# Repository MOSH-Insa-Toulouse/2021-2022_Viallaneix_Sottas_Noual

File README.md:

# 2021-2022_Viallaneix_Sottas_Noual MOSH Project 2022
Granulometric sensor

# Informations générales
> Ce projet s'inscrit dans le cadre de l'UF _"Du capteur au banc de test en open source hardware"_.
> Le cœur du projet bat sur la fréquence de la **LOW TECH**. Nous partirons de la fabrication d'un capteur granulométrique élaboré à partir d'une feuille de papier sur laquelle une couche de carbone sera déposée à l'aide d'un crayon à papier (panel de dureté entre HB et 9B) selon un motif prédeterminé. À ce corps d'épreuve, deux électrodes insérées aux extrémités du motif permettront la circulation d'un courant. Une déformation du capteur entraînera une variation du courant mesurable par un système d'acquisition de données. Les enjeux du projet sont donc multiples!
* **Physique** : sur les propriétés d'un capteur granulométrique
* **Technique** : sur la conception et le développement d'un système d'acquisition
* **Exploratoire** : par l'utilisation des outils et concepts de l'Open Source Hardware.
* **Se construire une composante _low-tech_  de l'ingénieur que nous serons** : en s'interrogeant sur les attentes d'une société en mutation, en posant un regard critique sur la notion de progrès technique et sa finalité.

# Ce que fait ce projet 

> La finalité du projet est de pouvoir estimer les forces et faiblesses de ces capteurs low-tech. Pour cela nous allons devoir les tester, déterminer leurs caractéristiques et leur limites d'utilisations.
> Pour y parvenir, nous allons concevoir un banc de mesures qui nous permettra, dans un premier temps, d'étalonner les capteurs (leurs sensibilités varient en fonction de la dureté) puis, dans un deuxième temps, de les éprouver dans des conditions et durées d'utilisation controlées.
> Les jeux de données issues de ces tests vont devenir rapidement conséquents et il sera utile de prévoir les scripts et la visualisation en sortie du banc de test et étalonnage. 
> La composante **étalonnage** du banc permet de détérminer la sensibilité un capteur de sensibilité inconnue. La composante **test** permet de soumettre le capteur à des séries de flexion/déflexion fonction d'un angle compris entre -85 et +85 degrés par rapport à la position d'équilibre.
> Dans la suite du projet le capteur désignera le corps d'épreuve et le banc de test permettant l'acquisition des données.

***
## Les axes du projets
* [Présentation du capteur granulométrique](#présentation-du-capteur-granulométrique)
* [Acquisition des données](#acquisition-des-données)
  * [Carte Arduino](#la-carte-arduino)
  * [Étude du circuit électrique](#le-conditionneur)
    * [Partie 1: Mesure d'un très faible courant avec l'aide d'un micro-contrôleur](#partie-1-mesure-dun-très-faible-courant-avec-laide-dun-micro-contrôleur)
       * [Vérification avec la Datasheet de l'AOP](#vérification-avec-la-datasheet-de-laop)
    * [Partie 2: Mise en oeuvre du filtrage du signal](#partie-2-mise-en-oeuvre-du-filtrage-du-signal)
    * [Schéma du circuit électronique final](#schéma-du-circuit-électronique-final)
    * [Partie 3: Simulations sous *LTSpice*](#partie-3-simulations-sous-ltspice)
  * [Code Arduino du système](#code-arduino-du-système)
  * [Application sur Android](#application-sur-android)
* [Réalisation du PCB](#réalisation-du-pcb)
   * [Partie 1: Conception de la schématique et des connexions entre les composants électroniques](#partie-1-conception-de-la-schématique-et-des-connexions-entre-les-composants-électroniques)
   * [Partie 2: Conception du PCB](#partie-2-conception-du-pcb)
   * [Partie 3: Soudure des composants sur le PCB et premiers tests](#partie-3-soudure-des-composants-sur-le-pcb-et-premiers-tests)
* [Banc de tests](#banc-de-tests)
* [Measurement System Analysis](#measurement-system-analysis)
* [Crédits](#auteurs)

***

### Présentation du capteur granulométrique
> Le capteur sélectionné dans le cadre de ce projet est un dépôt de graphite sur un papier, effectué à l’aide d’un crayon plus ou moins gras. 
Nous utiliserons pour cela la résistivité du graphite, qui est suffisamment faible pour laisser circuler un courant mesurable. Néanmoins, avec cette résistivité de 8 µΩ.m (contre 0,017 µΩ.m pour le cuivre), il faudra utiliser un montage amplificateur dans notre banc de test.

> Le dépôt de graphite effectué sur le papier sera alors représentatif de la flexion que ce dernier subit : les grains de graphite jouent le rôle de conducteur mais leur éloignement variera selon la flexion, et va donc influencer la résistance mesurée.

<div align="center">
</p>

**Figure 1: Première description schématique d'une mesure sur le capteur de graphite**

<div align="left"></p>

> Dans l’exemple ci dessus, on mesurera pour une même tension appliquée que:

<div align="center">
</p>

<div align="left"></p>

> L’intérêt de ce capteur se situe dans son aspect low-tech qui lui permet d’être facilement produit, mais pas uniquement :  la vaste gamme de dureté des mines de crayon (H, F, HB, B) offre un large choix pour la résistivité du dépôt.
En effet, la dureté d’une mine correspond à ses proportions de graphite et d’argile. Le graphite est, par exemple, plus présent dans un crayon dit « gras » de type B que dans un crayon de type H. Ainsi, nous disposons assez simplement d’un large panel de capteurs pour éventuellement les comparer à l’aide du banc de tests.

(#### Propriété d'un système granulaire)
### Acquisition des données
#### La carte Arduino

Dans notre projet, nous allons utiliser la carte Arduino UNO possédant le microcontrôleur ATMega328. 

<div align="center">
</p>

**Figure 2: Illustration de la carte Arduino UNO et Brochage de la carte Arduino**

<div align="left"></p>

Elle dispose de 6 entrées analogiques et de 14 broches numériques d'entrées/sorties. 
Pour pouvoir l'utiliser, on a juste à la connecter directement à l'ordinateur via le câble USB. 

La carte Arduino UNO possède les caractéristiques suivantes: 

* **Résolution**: 10 à 12 bits (1024 à 4096 points)
* **Pleine échelle (VRef)**: de 1.1 V à 5.0 V
* **Impédance de source max**: 1 kΩ à 10 kΩ
* **Fréquence d'échantillonnage**: 15 kHz maximale

#### Le conditionneur

#### Partie 1: Mesure d'un très faible courant avec l'aide d'un micro-contrôleur
L’objectif étant d’extraire l’information utile du capteur ayant un très faible courant (environ 100 nA), le montage électrique doit être adapté de manière à mesurer des courants faibles. Selon les caractéristiques techniques du microcontrôleur Arduino (cf Datasheet), on ne peut pas mesurer directement de très faibles courants en raison de l’impédance de source (environ égale à quelques kOhms). Il est donc nécessaire d’utiliser un circuit amplificateur transimpédance composé d’un amplificateur opérationnel AOP pour convertir un courant issu du capteur en une tension mesurable par le CAN (Convertisseur Analogique-Numérique) de l’Arduino UNO.

<div align="center"></p>
  
**Figure 3: Montage de transimpédance (ou convertisseur courant-tension)**
  
<div align="left"></p>

L’inconvénient d’un montage classique de transimpédance est qu’il nécessite une grande résistance pour amplifier le signal et que la tension d’alimentation du capteur doit être négative. On peut donc ajouter un autre étage inverseur à la suite du premier montage : 

<div align="center"></p>
  
**Figures 4 et 5: Ajout d'un étage inverseur sur le montage de transimpédance et Calcul du gain du second montage**

<div align="left"></p>

Dans le montage ci-dessus, le gain du second étage étant négatif compte-tenu de son caractère inverseur (`cf Figure 3`), la résistance R1 du premier étage n’a plus besoin d’avoir une grande valeur. De plus, l’alimentation du capteur est donc positive grâce au second montage inverseur du fait des produits des gains de deux étages. 

Pour plus de simplicité, on a choisi un montage en prenant un seul AOP dans le montage.

<div align="center"></p> 

**Figure 6: Solution simplifiée pour le montage transimpédance**

**Figure 7: Calcul de la tension aux bornes de R1**

<div align="left"></p>
  
En calculant la tension aux bornes de la résistance R1, on obtient une tension environ égale à 10 mV d'après la `Figure 4`.

Il s’agit d’une valeur importante pour le choix de l’AOP notamment pour l'effet de l’offset du signal d’entrée. 
Le Gain de ce montage et la Tension de sortie ADC sont décrits dans les calculs ci-dessous : 

<div align="center"> </p>
  
**Figure 8: Calculs du gain du montage et de la tension de sortie**

<div align="left"></p>
  
Si on a un courant nul en entrée, on veut alors obtenir une tension ADC nulle en sortie, cela implique qu’il n’y ait pas de dérives en tension de la part de l’AOP.
Les principales contraintes pour le choix de l’amplificateur opérationnel sont le faible courant d’entrée et un très faible offset de tension devant être négligeable devant 10mV (tension aux bornes de R1).

##### Vérification avec la Datasheet de l'AOP

Selon les données de la [Datasheet](LTC1050C.pdf) de l'AOP 1050C, on constate qu'il possède un faible offset de tension d'environ 5μV au maximum et un très faible drift pour l'offset de tension à environ 0.05μV/°C. Cela indique la bonne stabilité de l'amplificateur opérationnel. Par comparaison, les AOP utilisés traditionnellement en salle de TP possèdent un offset autour de 5mV, une valeur 1000 fois plus grande que celle du 1050C.
En comparant la tension d'entrée (autour de 10mV `cf Figure 5`), on constate que l'offset de 5μV est très faible.
De plus, on peut remarquer que cet AOP possède un mode commun incluant la masse ce qui correspond à notre montage électrique.
  
<div align="center"></p>

**Figure 9: Extrait de la datasheet dans la partie Electrical Characteristics**

<div align="left"></p>
  
Enfin, on constate que le courant de polarisation en entrée (Input Bias Current) est au maximum égale à 30pA, cela convient car nous effectuons des mesures de courant autour de 100nA. Il faut que le courant Isense `cf Figure 4` soit très faible devant 100nA et le reste du courant passe dans la résistance R1. 
En respectant les différentes conditions énoncées précédemment, l'AOP 1050C est adapté pour notre circuit électronique.

#### Partie 2: Mise en oeuvre du filtrage du signal

Étant donné que ce montage est très sensible aux signaux parasites (50Hz, horloge du microcontrôleur Arduino, Bluetooth entre autres), on doit mettre en œuvre un filtrage passe-bas pour limiter les perturbations du signal.
D’une part, il faut appliquer un filtre passif en entrée pour limiter les perturbations de type radiofréquences pouvant conduire à un excès de bruit dans l’ADC.
Ensuite, on applique un filtre actif au niveau de l’amplificateur opérationnel pour augmenter l’efficacité de l’échantillonnage du signal. 
À la sortie de l’AOP, on utilise un dernier filtre passif pour retirer le bruit sur le traitement du signal et les phénomènes de repliement de spectre (aliasing). 

En intégrant les différents filtres, le montage ressemble à ceci : 

<div align="center"></p>

**Figure 10: Schéma du montage électrique avec les différents filtres**

<div align="left"></p>

On distingue 3 différents filtres où nous avons cherché pour chacun la fréquence de coupure et son rôle principal pour le filtrage : 

<div align="center"></p>

**Figure 11: Identification des différents filtres dans le montage**

<div align="left"></p> 
 
Tout d'abord, le filtre passe-bas passif, placé à l'entrée de l'AOP, est constitué de R1(100kΩ) et C1(100nF). Il possède une fréquence de coupure théorique environ égale à 16Hz `cf Figure 7` . Il permet donc de filtrer les perturbations et les excès de bruit en courant sur la forme du signal d'entrée. 

<div align="center"></p> 

**Figure 12: Calcul de la fréquence de coupure du filtre passif (R1 et C1)**

<div align="left"></p>

Ensuite, le filtre passe-bas actif, placé entre l'entrée et la sortie de l'AOP, est constitué de R3(100kΩ) et C4(1μF) en parallèle. Ce dernier possède une fréquence de coupure théorique environ égale à 1.6Hz `cf Figure 8`. Son rôle principal est de supprimer la composante parasite de 50Hz (du fait du couplage capacitif avec la tension 230V) qui perturbe significativement le signal `cf Figure XX`.

<div align="center"></p>

**Figure 13: Calcul de la fréquence de coupure du filtre actif (R3 et C4)**

<div align="left"></p>

Enfin, le filtre passe-bas passif, placé à la sortie de l'AOP, est constitué de R6(100kΩ) et C2(100nF). Il possède une fréquence de coupure théorique environ égale à 1.6kHz `cf Figure 9`. En sachant que la fréquence d'échantillonnage du micro-contrôleur est environ égale à 15,4kHz, il faut respecter la condition d'échantillonnage de Shannon à savoir:  

<div align="center"></p> 

</p>
</p>
</p>

**Figures 14: Calcul de la fréquence de coupure du filtre passif (R6 et C2) et Vérification de la condition d'échantillonnage de Shannon**

<div align="left"></p>

Selon les calculs, on respecte bien la condition d'échantillonnage de Shannon `cf Figure ci-dessus`, le filtre permet de limiter les effets de repliement de spectre (rôle d'anti-aliasing) et de manière générale, le bruit lors du traitement du signal. 

#### Schéma du circuit électronique final
> Voici un première proposition du schéma électrique
  
<div align="center"></p>

**Figure 15: Premier schéma du montage électronique**

<div align="left"></p>
  
Dans ce schéma, nous simulons le bruit en courant à l'entrée en mettant une capacité à côté du générateur de tension. On a ajouté une capacité C3 pour filtrer le bruit de la source d'alimentation.
  
> On propose une optimisation du montage électronique en simulant le capteur de graphite `cf Figure ci-dessous`
  
<div align="center"></p>

**Figure 16: Schéma électrique optimisé**

<div align="left"></p>
  
Nous avons simulé notre capteur de graphite (cf rectangle en haut à gauche de la `figure précédente`). 
> Commentaires à ajouter

#### Partie 3: Simulations sous *LTSpice*
  
On vérifie les conditions optimales de fonctionnement du montage électronique en effectuant différentes simulations sur le logiciel *LTSPice* `cf figures ci-dessous`.

<div align="center"></p>
</p>

**Figure 17: Vérification du gain d'amplification du signal environ égal 100**
  
</p>

**Figure 18: Vérification du la tension de sortie du montage avec un courant d'entrée égal à 100nA**

<div align="left"></p>
  
Pour l'illustration graphique du gain du montage général, on distingue qu'il y a bien 3 filtres dans le circuit électronique grâce aux différentes variations du terme de phase (courbe en traits en pointillés `cf Figure ci-dessous`).

<div align="center"></p>
</p>

**Figure 19: Identification graphique des 3 filtres**

<div align="left"></p>

> On vérifie graphiquement la fréquence de coupure de chaque filtre en effectuant une simulation fréquentielle (AC Sweep):

Pour le premier filtre à l'entrée de l'AOP (R1 et C1):
<div align="center">
</p>

**Figure 20: Illustration graphique de la fréquence de coupure du filtre (R1 et C1)**

<div align="left"></p>
  
Pour le second filtre entre l'entrée et la sortie de l'AOP (R3 et C4) et le dernier filtre à la sortie (R6 et C2):
  
<div align="center">
</p>

**Figure 21: Illustration graphique des fréquences de coupure des deux filtres passe-bas**

<div align="left"></p>

> On vérifie l'incidence du courant d'entrée de l'amplificateur sur la tension de sortie par une simulation temporelle:

<div align="center">
</p>

**Figure 22: Illustration graphique de l'incidence du courant d'entrée sur la tension de sortie**

<div align="left"></p>
  
On peut remarquer dans cette image qu'à partir d'une valeur de 500nA pour le courant d'entrée, on obtient une tension pouvant saturer le convertisseur analogique-numérique de l'Arduino. 

> On observe graphiquement l'atténuation globale du signal d'un bruit en courant de 50 Hz ainsi que celle associée à un bruit en courant à la fréquence de repliement de spectre autour de 7 kHz. 

<div align="center">
</p>

**Figures 23 et 24: Illustration graphique de l'atténuation du signal d'un bruit en courant pour deux fréquences spécifiques et calculs des atténuations**

<div align="left"></p>

Comme on peut le voir avec les calculs précédents, on constate qu'il y a une atténuation en bruit de courant environ égale à 40dB pour une fréquence autour de 50Hz et elle est environ égale à 100 dB pour un bruit en courant au voisinage de la fréquence de repliement de spectre. Cela montre bien que le signal peut être fortement perturbé et atténué si on laisse la composante fréquentielle à 50 Hz et si on ne respecte la condition d'échantillonnage.   

### Code Arduino du système
<div align="center">
</p>

**Figure 25: Logigramme de notre code Arduino**

<div align="left"></p>
  
Voici une présentation graphique de notre code Arduino.
  
### Application sur Android

L'application mobile associée au banc de test fonctionne avec un timer identique à celui du programme Arduino. L'utilisateur peut se connecter au module Bluetooth de son choix, puis vérifie que la connexion est bien établie avec un second bouton. Il peut ensuite lancer la mesure et afficher les résultats reçus sur un graphe en temps réel, afin de suivre l'évolution de la résistance du capteur. Le graphe reprend du début lorsque le balayage atteint le bout de l'écran, mais l'utilisateur peut le réinitialiser à sa guise avec un autre bouton. Enfin, la mesure peut être arrêtée en appuyant à nouveau sur le bouton qui l'a déclenché.

<div align="center"></p>
</p>

**Figure 26: Aperçu visuel de notre application**

<div align="left"></p>

<div align="center">
</p>
</p>

**Figures 27 et 28: Extraits des blocs pour la réalisation de l'application Android sur *MIT App Inventor***

<div align="left"></p>   

### Réalisation du PCB

Après avoir réalisé les simulations sur *LTSpice*, nous avons conçu un premier modèle de PCB avec l'aide du logiciel *KiCAD*. 

#### Partie 1: Conception de la schématique et des connexions entre les composants électroniques

> Lors de cette étape, nous avons choisi un modèle basé sur l'Arduino UNO pour avoir les bonnes dimensions de la carte et les pins de connexion adéquats. Afin de réaliser précisément le PCB, nous avons dû concevoir certains composants électroniques nous-mêmes dans la partie Schématique (écran OLED, module Bluetooth, l'amplificateur LTC1050C, l'encodeur rotatoire et le potentiomètre digital)  `cf Figures ci-dessous`

<div align="center">
</p>

**Figure 29: Schéma des pins de connexion de la carte Arduino UNO **

</p>
 
**Figure 30: Schéma du circuit électronique**
 
</p>
</p>
</p>
</p>

**Figures 31: Schémas et empreintes de chacun de nos composants électroniques (Écran OLED, BLuetooth, Encodeur rotatoire, Potentiomètre digital)**

<div align="left"></p>

#### Partie 2: Conception du PCB

> Dans cette partie, nous plaçons virtuellement les différents composants sur le PCB et nous effectuons toutes les connexions entre les pins de composants et ceux de la carte Arduino. Nos différents professeurs réferents (Mr Jérémie Grisolia et Mme Catherine Crouzet) nous ont indiqués les consignes à respecter pour la réalisation du PCB: 
  
* Largeur des pistes = 0.6 mm
* Largeur d'isolation des pistes = 0.9 mm
* Dimensions du trou pour l'écran OLED, le module Bluetooth et l'encodeur rotatoire = 2 mm * 2.5 mm
* Diamètre du via (trou entre la face avant et arrières du PCB) = 2 mm
* Taille du trou de perçage du via = 0.8 mm
* Taille du trou de perçage pour l'écran OLED, le module Bluetooth et l'encodeur rotatoire, l'AOP et le potentiomètre digital = 1 mm
* Dimensions du trou pour le support de l'AOP (pad n°1 rectangulaire et les autres pins sont ovales) = 2 mm * 2.5 mm
* Taille du trou de perçage pour les résistances et les capacités = 0.8 mm
  
<div align="center">
</p>

**Figure 32: Schémas des pistes sur le PCB**

<div align="left"></p>

<div align="center">
</p>

**Figure 33: Schéma 3D des pistes sur le PCB**

<div align="left"></p>
  
Avec l'aide de Mme Catherine Crouzet, nous avons réalisé le PCB selon le protocole suivant:

* Insolation de la plaque de résine positive par photo-lithographie UV par contact avec un masque `cf Figure ci-dessous` imprimé sur un film transparent, provenant du logiciel *KiCAD*. Cette résine est choisie de telle manière à être sensible aux rayons UV.
Une fois l'insolation réalisée, la partie de la résine insolée est dissoute dans une solution de développeur. Le reste de la résine, étant protégé par le masque, reste intact. On observe l'apparition des pistes du circuit sur le PCB.
  
* Passage dans un bain de péroxyde de fer pour enlever les résidus de la piste de cuivre sur le PCB
  
* Nettoyage et Séchage de la plaque à l'eau naturelle

<div align="center">
</p>

**Figure 34: Masque imprimé du PCB sur un film transparent**

<div align="left"></p>

#### Partie 3: Soudure des composants sur le PCB et premiers tests
 
Uns fois le PCB réalisé, nous avons percé tous les trous des pins associés à chaque composant électronique puis nous avons soudé les différents composants et les broches latérales entre le PCB et la carte Arduino.

### Banc de tests

> Le but de ce banc de test est de déterminer la sensibilité du capteur, de voir l’évolution de cette dernière selon la répétition des flexions et de comparer ces données avec un capteur commercialisé "Flex-Sensor".

> Ce banc de test est composé d’un servomoteur pour une bonne précision sur les angles, ainsi que d’un support où l’on vient encastrer le capteur. Une roue où l’on positionne le bout du capteur est alors entraînée par le servomoteur et génère la flexion. Il est fait de plaques de contreplaqué superposées, qui ont été découpées au FabLab et il permet de garder le capteur le plus intact possible, car celui-ci n’est maintenu qu’aux deux extrêmités et non pas sur le dépôt de graphite lui-même.
L’utilisateur détermine au préalable le nombre de répétitions souhaité à l’aide de l’encodeur rotatoire placé sur le PCB. Il peut ensuite récupérer les données (angle, itération de la mesure, résistance lue) sur le moniteur série et les traiter dans un logiciel comme Rmarkdown, Python via l'interpréteur Spyder IDE ou Qtiplot.
Le capteur qui servira de référence comparative sera le Flex Sensor fourni dans le kit Arduino, qui possède déjà une datasheet.

> Nous avons élaboré un premier modèle en 2D ainsi qu'un modèle 3D de notre banc de tests: 
<div align="center"></p>

**Figure 35: Dessin 2D du banc de test**

<div align="left"></p>
<div align="center"></p>

</p>

**Figure 36: Dessin 3D du banc de test sur *FreeCAD***

<div align="left"></p>

> Nous l'avons ensuite réalisé au FabLab avec l'aide d'une découpe laser: 

<div align="center">
</p>

**Figure 37: Réalisation du banc de test au FabLab**

<div align="left"></p>

Nous avons ensuite effectué les premiers tests sur notre banc de tests avec notre capteur: 

<div align="center">
</p>

**Figure 38: Premiers tests avec notre banc de tests**

<div align="left"></p>

### Measurement System Analysis

### Auteurs

Arona SOTTAS, Léo VIALLANEIX et Raphaël NOUAL

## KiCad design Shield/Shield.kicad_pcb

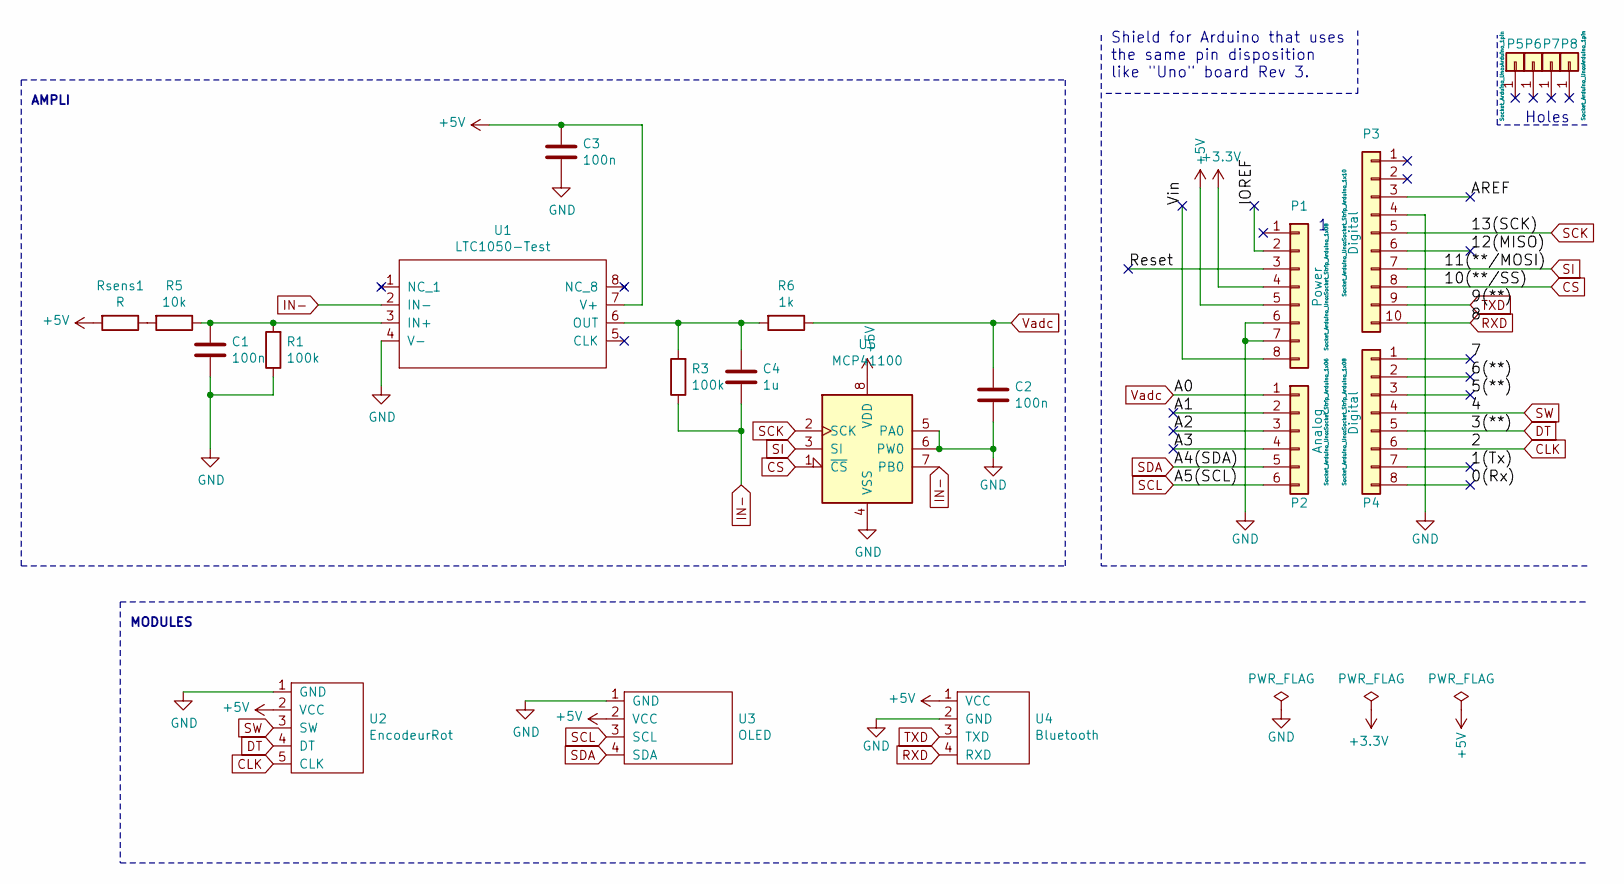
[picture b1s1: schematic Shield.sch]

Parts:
C1, C2, C3: 100n; C_Disc_D3.0mm_W1.6mm_P2.50mm
C4: 1u; C_Rect_L7.0mm_W4.5mm_P5.00mm
P1: Power; Socket_Strip_Arduino_1x08
P2: Analog; Socket_Strip_Arduino_1x06
P3: Digital; Socket_Strip_Arduino_1x10
P4: Digital; Socket_Strip_Arduino_1x08
P5, P6, P7, P8: CONN_01X01; Arduino_1pin
R1, R3: 100k; R_Axial_DIN0207_L6.3mm_D2.5mm_P10.16mm_Horizontal
R5: 10k; R_Axial_DIN0207_L6.3mm_D2.5mm_P10.16mm_Horizontal
R6: 1k; R_Axial_DIN0204_L3.6mm_D1.6mm_P7.62mm_Horizontal
Rsens1: R; Sensor
U1: LTC1050-Test; LTC1050
U2: EncodeurRot
U3: OLED
U4: Bluetooth
U5: MCP41100

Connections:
+3V3: P1.4
+5V: C3.2, P1.5, Rsens1.2, U1.7 (V+), U2.2 (VCC), U3.2 (VCC), U4.1 (VCC), U5.8 (VDD)
/0(Rx): P4.8
/1(Tx): P4.7
/5(**): P4.3
/6(**): P4.2
/7: P4.1
/12(MISO): P3.6
/A1: P2.2
/A2: P2.3
/A3: P2.4
/AREF: P3.3
/IOREF: P1.2
/Reset: P1.3
/Vin: P1.8
CLK: P4.6, U2.5 (CLK)
CS: P3.8, U5.1 (~CS)
DT: P4.5, U2.4 (DT)
GND: C1.2, C2.2, C3.1, P1.6, P1.7, P3.4, R1.1, U1.4 (V-), U2.1 (GND), U3.1 (GND), U4.2 (GND), U5.4 (VSS), U5.5 (PA0), U5.6 (PW0)
IN-: C4.2, R3.1, U1.2 (IN-), U5.7 (PB0)
unnamed: C1.1, R1.2, R5.1, U1.3 (IN+)
unnamed: C4.1, R3.2, R6.2, U1.6 (OUT)
unnamed: R5.2, Rsens1.1
RXD: P3.10, U4.4 (RXD)
SCK: P3.5, U5.2 (SCK)
SCL: P2.6, U3.3 (SCL)
SDA: P2.5, U3.4 (SDA)
SI: P3.7, U5.3 (SI)
SW: P4.4, U2.3 (SW)
TXD: P3.9, U4.3 (TXD)
Vadc: C2.1, P2.1, R6.1

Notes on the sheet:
Holes
Shield for Arduino that uses the same pin disposition like "Uno" board Rev 3.
AMPLI
MODULES

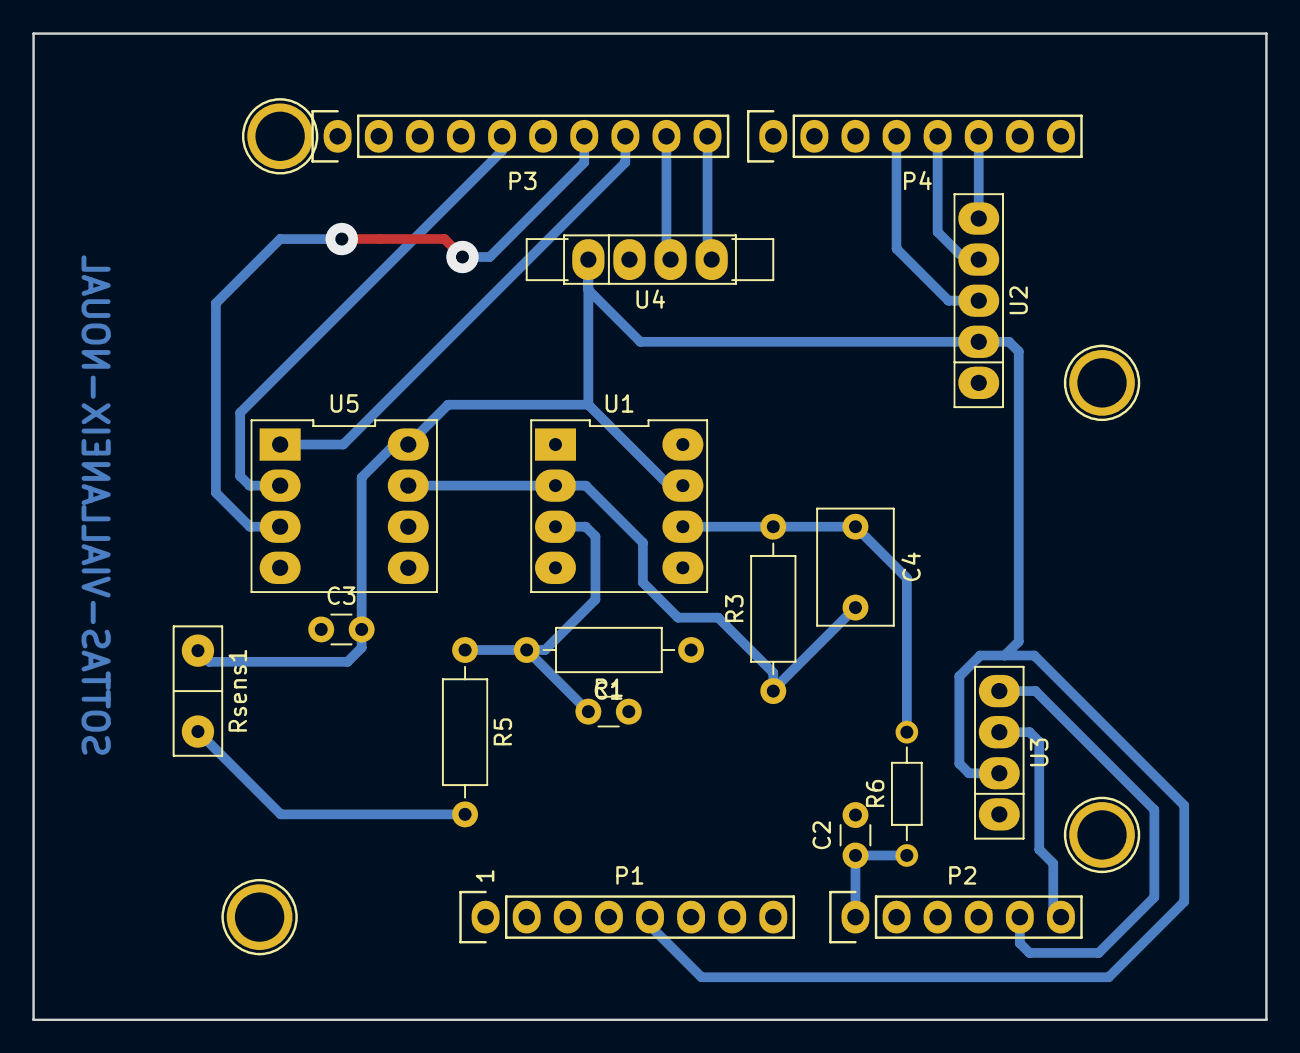
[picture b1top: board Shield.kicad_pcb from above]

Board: 2 copper layers, 76.2 x 61.0 mm, 22 parts (0 on the bottom side), 17 nets.

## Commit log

2022-03-06 Première modification du README
2022-03-06 Premier jet - 06-03-2022 -# Please enter the commit message for your changes. Lines starting -
2022-03-06 Code base projet MOSH
2022-03-06 Premier essai
2022-03-16 Modication section capteur
2022-03-16 Modificatiion 3 section capteur
2022-04-06 Create KiCad files
    Fichiers servant à la réalisation du PCB
2022-04-06 KiCAD PCB
2022-04-08 Modification du programme : Pin B de l'encodeur supprimée et pin 4 du switch basculé sur pin 3 pour gérer les 2 interrupt dispo en 2 et 3.
2022-04-12 Ajout folders Shield & Images
2022-04-12 Changes by Leo Viallaneix
2022-04-15 Changes APK Bluetooth
2022-04-15 Organisation dossier Images
2022-04-16 Création Dossier PCB
2022-04-16 bis creation dossier PCB
2022-04-16 Suppression Shield.zip & création .gitignore
2022-04-16 Déplacement dans le dossier image
2022-04-16 Images de l'apk par Léo
2022-04-16 ajout programmes banc de test
2022-04-16 ajout apk sur le .gitignored
2022-04-16 Images de l'application par Léo
2022-04-16 Programme Sans banc de test
2022-04-16 Update ignore
2022-04-16 Suppressions anciens commentaires
2022-04-16 Dépot du Rmarkdown pour MSA (Measurement System Analysis)
2022-04-16 Version html de l'analyse MSA
2022-04-17 Create PCB
2022-04-17 Ajout Images/PCB/
2022-04-18 ajout pgm version PCB & banc arduinos indep.
2022-04-18 Test clean nouvelle branche
2022-04-18 clean branche fixing issues
2022-04-18 Ajout du debounce et delay(50)
2022-04-18 Delay(50) et debounce
2022-04-18 Blocs de l'application sur MitAppInventor
2022-04-18 Face avant de l'application
2022-04-18 Version finale de l'arduino
2022-04-18 pgm banc géré par interrupts
